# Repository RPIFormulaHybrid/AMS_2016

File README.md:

This is a test of the GIT merge
The quick brown Fox 
Jumps Over the lazy dog
Ending test of GIT merge

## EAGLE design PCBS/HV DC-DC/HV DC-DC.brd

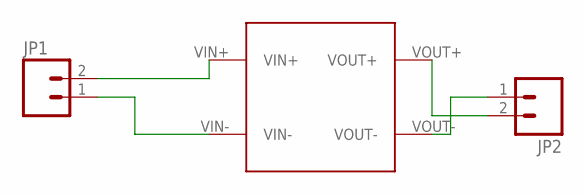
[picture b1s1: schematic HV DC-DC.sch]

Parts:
JP1, JP2: M02LOCK; 1X02_LOCK
U$1: RUW15SL12C

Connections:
unnamed: JP1.1, U$1.VIN-
unnamed: JP1.2, U$1.VIN+
unnamed: JP2.1, U$1.VOUT-
unnamed: JP2.2, U$1.VOUT+

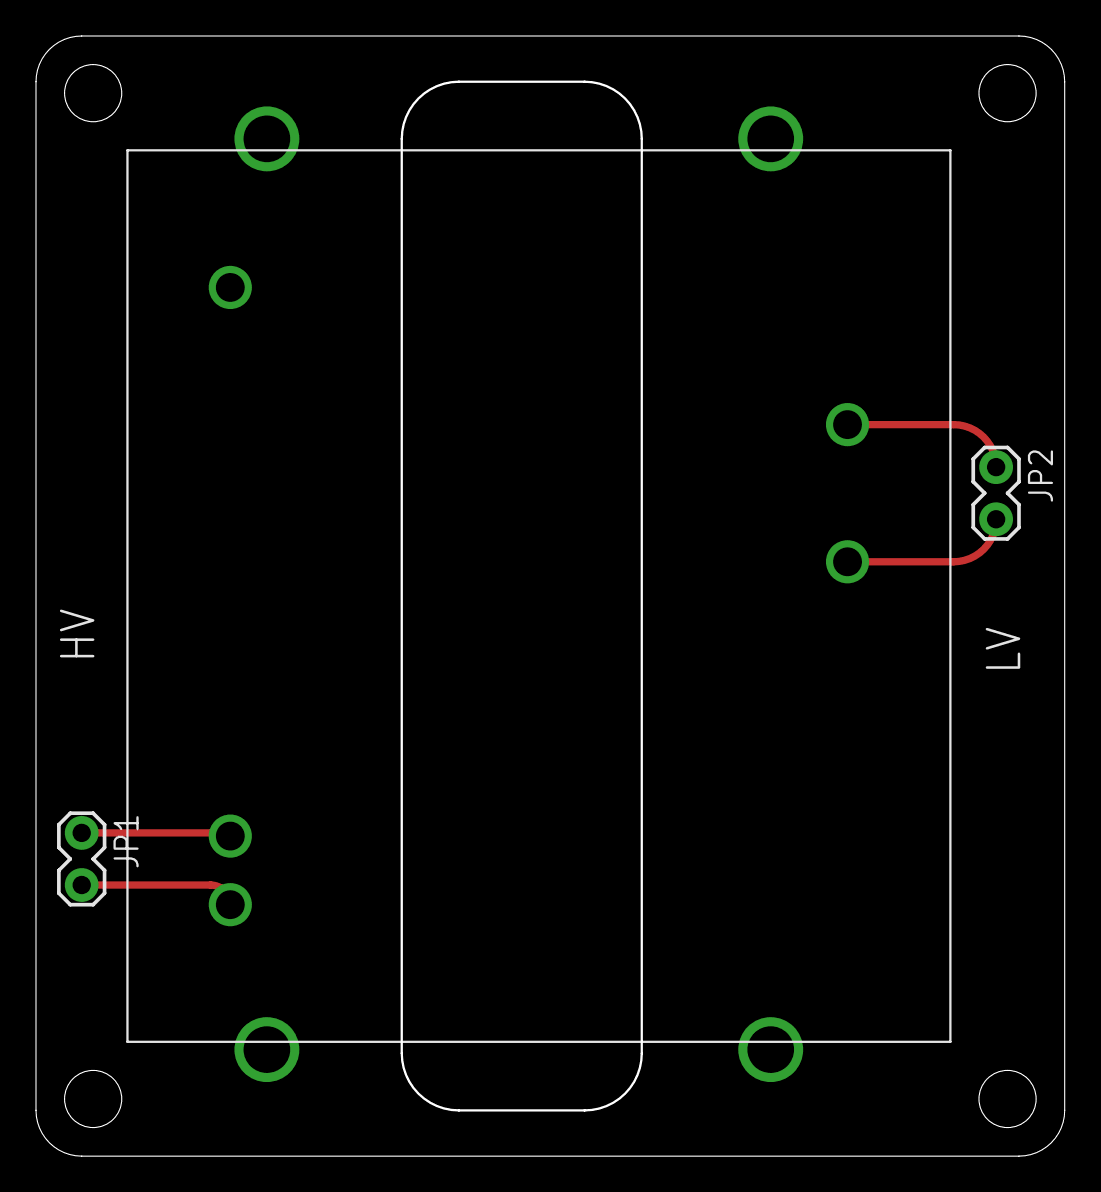
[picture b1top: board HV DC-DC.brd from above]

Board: 2 copper layers, 57.0 x 62.1 mm, 3 parts (0 on the bottom side), 4 nets.

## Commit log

2016-01-23 Create String Monitoring Board
2016-01-23 Create Mother uC
2016-01-23 Rename String Monitoring Board to SMB uC
2016-01-23 Create Comm uC
2016-01-23 Rename Comm uC to Comm uC.ino
2016-01-23 Rename Mother uC to Mother uC.ino
2016-01-23 Rename SMB uC to SMB_uC.ino
2016-01-23 Rename Comm uC.ino to Comm_uC.ino
2016-01-23 Rename Mother uC.ino to Mother_uC.ino
2016-02-12 Test of adc and work on hv dc-dc interface board
2016-02-15 Upload of Library from MCP3423
2016-02-16 Update Library
2016-02-16 Changed a README word
    That's it
2016-02-16 Capitalized word in README
2016-02-16 Tried to mess up the README
2016-02-16 Test Change of README
2016-03-06 Began coding Comm processor
    Outlined code, started on smaller functions
2016-03-11 Upload of LTC6802 Test
2016-03-21 CodeUpdate
2016-04-02 Initial code structure for program added
2016-04-10 Working Test Code To Read 6 Cells from LTC
2016-04-10 Test of Optimos added in
2016-04-10 SMB_uC
    Added primary SMB code file.
2016-04-14 Updated SMB_uC
    Added code for LTC and ADC. Added ADC addresses for the remaining inputs
2016-04-18 Updates to SMB code
    Code changes reflecting communication testing between the Motherboard
    and SMB
2016-04-21 Mother Code in progress
2016-04-21 dingle commmit
2016-04-21 Added lots of comm code
    Added LED states and data receive states
2016-04-21 remove smb_uc from szymon branch
2016-04-23 SMB code crit. update
    Figured it out at last. Can finally properly interface with the world's
    most annoying ADC. Should print all cell and temp measurements, not yet
    set up to send it over I2C yet
2016-04-24 Semi-final SMB code
    Working communication with motherboard. Alternating temperature/voltage
    information on every call. Always 24 bytes.
2016-04-24 WireTest has successful code
    Code is able to communicate with SMB and successfully read cell voltages
    and temps from it
2016-04-26 Able to communicate with 4 smbs
2016-04-26 Running SMB code
    Still needs optimization, watchdog timer
2016-04-27 SMB minus balancing
    Car ready
2016-05-01 Basic Functional Code for TSAC
    -need to test with full pack
    -need to add in cell check prior to mode change on mother
2016-05-05 updated mother code
2016-05-05 Minor changes
2016-05-07 Working Code
2016-05-07 Fixed some redundant lines
2016-06-03 code dump
2017-04-15 added define for SMB Board ID, added indication for when balancing is happening
2017-04-20 temp commit
2017-04-26 test code

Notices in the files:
parts and their libraries:
SparkFun-Connectors: Licensing: Creative Commons ShareAlike 4.0 International - https://creativecommons.org/licenses/by-sa/4.0
